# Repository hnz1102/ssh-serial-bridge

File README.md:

<div align="center">
  <h1><code>SSH Serial Bridge</code></h1>
  
</div>

# ssh-serial-bridge - SSH-to-Serial Bridge for Raspberry Pi, USB CDC and UART

Firmware for the ESP32-S3 that bridges an SSH connection (over Wi-Fi) to UART
and USB CDC serial ports.  Written in Rust (esp-idf-hal / esp-idf-svc) with a
C component (wolfSSH) for the SSH server.

## Features

| Feature | Description |
|---------|-------------|
| SSH server | Port 22, username/password authentication via wolfSSH, multiple concurrent sessions (including shared sessions on the same serial port) |
| Serial ports | COM1 / COM2 (UART) and USB CDC (USB Host) — up to 4 ports (`usb0`–`usb3`) |
| Web UI | Browser-based configuration, terminal, and GPIO control |
| WebSocket terminal | Built-in xterm.js; access serial data from the browser at `/terminal` |
| WPS support | Wi-Fi Protected Setup (PBC mode) — configure Wi-Fi via button or Web UI |
| GPIO / PWM | Digital output (ON/OFF) on GPIO 4–9, 12 ; PWM output on GPIO 10–11 |
| SPI display | Optional ST7789V (320×240) display showing incoming serial data |
| UDP Syslog | RFC 5424 remote logging over UDP |
| NTP | Time synchronisation on boot; up to 4 servers configurable via Web UI |
| NVS settings | Persistent configuration stored in NVS; editable via Web UI at runtime |

---

## Architecture

```
SSH client ──[TCP:22]──► ssh_bridge.c (wolfSSH)
                               │
        per-session ring buffers (PSRAM)
                               │
Rust usb_host.rs ◄─────────────┘
 ├── COM1 (UART1)
 ├── COM2 (UART2)
 └── USB CDC (USB Host: PL2303 / FTDI / etc.)

Browser ──[HTTP/WS]──► httpserver.rs
 ├── /terminal  (xterm.js + WebSocket /ws/serial)
 ├── /          (configuration page)
 └── /gpio      (GPIO/PWM control page)
```

---

## Directory Layout

```
ssh-serial-bridge/
├── src/
│   ├── main.rs           # Entry point, peripheral initialisation
│   ├── usb_host.rs       # USB Host (PL2303 etc.) + UART + SSH bridge control
│   ├── httpserver.rs     # HTTP/WebSocket server, NVS config management
│   ├── wifi.rs           # Wi-Fi STA connection (DHCP / static IP)
│   ├── syslogger.rs      # UDP Syslog logger (RFC 5424)
│   ├── serial_display.rs # ST7789V SPI display rendering
│   ├── gpio_ctrl.rs      # Shared GPIO / PWM state
│   ├── btn_ctrl.rs       # GPIO0 button (short press: page cycle; long press: factory reset)
│   └── boot_log.rs       # NVS boot counter and rolling reset-reason log (last 10 entries)
├── components/
│   ├── ssh_bridge/       # SSH server C component (wolfSSH wrapper)
│   ├── wolfssh/          # wolfSSH (github.com/wolfSSL/wolfssh, commit 157cb01f)
│   └── wolfssl/          # wolfSSL/wolfCrypt (github.com/wolfSSL/wolfssl, commit b7e7e755)
├── static/               # Embedded static files (xterm.js / css / fit addon)
├── cfg.toml              # Build-time default configuration (gitignored — contains credentials)
├── cfg.toml.<board>      # Board-specific templates (e.g. ssh-bridge-board / xiao-esp32s3)
├── sdkconfig.defaults    # ESP-IDF build settings
├── partitions.csv        # Flash partition table
├── build-flash-images.sh # Build merged flash + app-only OTA images per board
├── setup_components.sh   # Initial setup script for components/
└── setup_env.sh          # One-shot environment setup (Rust, espup, udev)
```

---

## Pin Assignment

### UART Serial

| Port | Signal | Default GPIO | XIAO-ESP32S3 |
|------|--------|-------------|--------------|
| COM1 | TX     | 17          | 43           |
| COM1 | RX     | 18          | 44           |
| COM2 | TX     | 19 (41)     | —            |
| COM2 | RX     | 20 (42)     | —            |

### GPIO / PWM Output

| GPIO    | Function |
|---------|----------|
| 4–9, 12 | Digital output ON/OFF |
| 10–11   | PWM output (LEDC, 1 kHz, 14-bit) |

### SPI Display (ST7789V)

| Signal | GPIO |
|--------|------|
| SCLK   | 48   |
| MOSI   | 45   |
| CS     | 40   |
| DC     | 39   |
| RST    | 38   |

### Button

| GPIO     | Function |
|----------|----------|
| 0 (BOOT) | Short press (<3 s): Cycle display page / Medium press (3–10 s): Toggle DC OUT (GPIO12) / Long press (≥10 s): NVS factory reset |
**Factory Reset Display Indicators:**
- **6–10 seconds** (button held): Display shows "FACTORY RESET" with countdown "Resetting to defaults in X seconds..."
- **10 seconds** (trigger): Display shows "FACTORY RESET" / "Erasing NVS... Please wait..." and device reboots
---

## Configuration

### Board-specific cfg.toml (build-time defaults)

Before building, choose a board config and copy it to `cfg.toml`.

- `ssh-bridge-board`: Board with a 2.0-inch TFT display for serial data output
- `mini-ssh-bridge-board`: Small-display board using SSD1306
- `xiao-esp32s3`: XIAO ESP32S3 board

```bash
# 2.0-inch TFT display board
cp cfg.toml.ssh-bridge-board cfg.toml

# SSD1306 mini display board
cp cfg.toml.mini-ssh-bridge-board cfg.toml

# XIAO ESP32S3 board
cp cfg.toml.xiao-esp32s3 cfg.toml
```

After copying, edit `cfg.toml` for your environment (Wi-Fi credentials, IP, etc.) if needed.

```toml
[ssh-serial-bridge]
wifi_ssid      = "your-ssid"
wifi_psk       = "your-password"
ip_mode        = "dhcp"           # "dhcp" or "static"
ip_address     = "192.168.2.200"
subnet_mask    = "255.255.255.0"
gateway        = "192.168.2.1"
dns            = "1.1.1.1"

syslog_server    = "192.168.2.140:514"
syslog_enable    = "false"
syslog_host_name = "esp32s3"
syslog_app_name  = "ssh-bridge"

ssh_user     = "admin"
ssh_password = "sshpass"

com1_tx_pin = "17"    # XIAO-ESP32S3: 43
com1_rx_pin = "18"    # XIAO-ESP32S3: 44
com1_baud   = "115200"
com2_tx_pin = "41"
com2_rx_pin = "42"
com2_baud   = "115200"

cdc_enable = "false"
cdc_baud   = "115200"

# CDC retry settings (for slow-initializing devices like Raspberry Pi USB Gadget)
cdc_retry_enable   = "true"    # Automatically retry CDC-ACM init until device is ready
cdc_retry_interval = "5"       # Seconds between retries (recommended: 5)

display_enable = "false"
display_port   = "com1"    # "com1" / "com2" / "usb0" / "usb1" / "usb2" / "usb3"

pwm_enable = "true"

# NTP servers (up to 4, in priority order)
ntp_server1 = "time.aws.com"
ntp_server2 = "time.google.com"
ntp_server3 = "time.cloudflare.com"
ntp_server4 = "ntp.nict.jp"

adc_conversion_factor = "74.47"　＃Factor to convert ADC reading to voltage (depends on voltage divider and reference voltage)
```

Values in `cfg.toml` are compiled into the firmware as defaults.  
After boot they can be overridden via the Web UI or direct NVS writes; NVS values take priority.

---

## Wi-Fi Setup with WPS

**WPS (Wi-Fi Protected Setup)** allows you to connect to a Wi-Fi network without manually entering the SSID and password. This device supports **WPS Push Button Configuration (PBC)** mode.

### Method 1: Using cfg.toml and Factory Reset (Recommended for initial setup)

If you don't have Wi-Fi credentials yet or want to reconfigure via WPS without Web UI access:

1. **Edit `cfg.toml` before building** (or rebuild the firmware):
   ```toml
   wifi_ssid      = ""           # Set to empty string
   wps_enable     = "true"       # Enable WPS mode on boot
   ```

2. **Flash the firmware** to the device

3. On boot, the device will automatically enter WPS mode and wait for you to **press the WPS button on your Wi-Fi router** (timeout: 2 minutes)

4. Upon successful WPS connection, the credentials are saved to NVS and the device reboots

**Alternative: Trigger WPS via Factory Reset**

If the device is already running with Wi-Fi configured but you want to switch to WPS:

1. **Edit `cfg.toml`** to set `wps_enable = "true"` and `wifi_ssid = ""`
2. **Rebuild and flash** the firmware
3. **Perform a Factory Reset**: Press and hold the BOOT button (GPIO 0) for **≥10 seconds**
4. The device will erase NVS, restore `cfg.toml` defaults, and reboot into WPS mode
5. **Press the WPS button on your Wi-Fi router** within 2 minutes

> **Note**: Web UI is not accessible until Wi-Fi is connected, so this method is essential for initial setup or when you lose Wi-Fi access.

---

### Method 2: Using the Web UI (when already connected to Wi-Fi)

1. Navigate to the configuration page at `http://<device_ip>/`
2. Find the **WPS** section
3. Click the **"Start WPS"** button
4. **Press the WPS button on your Wi-Fi router** within 2 minutes
5. The device will automatically receive and save the Wi-Fi credentials and reboot

### WPS Status Indicators

When WPS is active:
- **Display (if enabled)**: Shows "WPS MODE" with countdown timer (120 seconds)
  - "Press WPS button on your router within 120 seconds"
  - Countdown updates every 10 seconds
  - On success: "WPS SUCCESS" → "Connecting to {SSID}" → "CONNECTED"
- **Syslog (if enabled)**: Logs WPS start, success, or failure events
- **Web UI**: Shows WPS status during the connection process

### WPS Fallback

If WPS fails or times out, the device will revert to the previously configured Wi-Fi credentials (from `cfg.toml` or NVS).

### Notes

- WPS PBC mode is the only supported WPS method (PIN mode is not supported)
- After successful WPS configuration, the new credentials are saved to NVS and persist across reboots
- You can still manually configure Wi-Fi credentials via `cfg.toml` or the Web UI if WPS is not available on your router

---

## Environment Setup

Run `setup_env.sh` **once** on a fresh Ubuntu / Debian machine (or WSL2) before
building.  The script performs all steps below automatically.

```bash
bash setup_env.sh
```

After the script finishes, open a new terminal (or reload your shell config) so
the environment variables take effect:

```bash
source "$HOME/.cargo/env"
source ~/export-esp.sh
```

### What the script does

| Step | Action |
|------|--------|
| 1 | Install system packages via `apt` |
| 2 | Install Rust toolchain via `rustup` (skipped if already present) |
| 3 | Install `ldproxy`, `espup`, `cargo-espflash` via Cargo |
| 4 | Install & update the ESP32-S3 Xtensa toolchain via `espup` |
| 5 | Source `~/export-esp.sh` (generated by `espup`) |
| 6 | Add udev rule for ESP32 USB device (`303a:1001`) and reload rules |

> If you prefer to run the steps manually, expand each step below.

<details>
<summary>Manual setup steps</summary>

```bash
# 1. System packages
sudo apt update && sudo apt -y install \
    git python3 python3-pip gcc build-essential curl \
    pkg-config libudev-dev libtinfo5 clang libclang-dev \
    llvm-dev udev libssl-dev python3.10-venv

# 2. Rust
curl --proto '=https' --tlsv1.2 -sSf https://sh.rustup.rs | sh
# Select option 1 (default install), then:
source "$HOME/.cargo/env"

# 3. Cargo tools
cargo install ldproxy
cargo install espup
cargo install cargo-espflash

# 4. ESP32-S3 toolchain
espup install
espup update

# 5. Activate ESP environment (add to ~/.bashrc / ~/.zshrc for persistence)
. ~/export-esp.sh

# 6. udev rules
sudo sh -c 'echo "SUBSYSTEMS==\"usb\", ATTRS{idVendor}==\"303a\", ATTRS{idProduct}==\"1001\", MODE=\"0666\"" > /etc/udev/rules.d/99-esp32.rules'
sudo udevadm control --reload-rules
sudo udevadm trigger
```

</details>

---

## Build and Flash

### Prerequisites

- Rust toolchain: `esp` channel (selected automatically via `rust-toolchain.toml`)
- [espup](https://github.com/esp-rs/espup) — ESP32-S3 Xtensa toolchain
- [espflash](https://github.com/esp-rs/espflash)

### Initial component setup

Run once after cloning, or after a clean wipe of `components/`:

```bash
cd esp32-s3/ssh-serial-bridge
bash setup_components.sh
```

This clones wolfssh and wolfssl at the verified commits and places the
ESP-IDF-specific `CMakeLists.txt` and `include/user_settings.h` on top.

### Build

```bash
cargo build --release
```

### Flash and monitor

```bash
espflash flash --release --monitor
```

### Creating a complete flash binary image

To create a single binary file that includes all partitions (bootloader,
partition table, data partitions, and the currently built app image) for
distribution or web-based flashing:

```bash
cargo espflash save-image --release --merge --chip esp32s3 complete_flash.bin
```

This creates a complete 8 MB flash image starting from offset 0x0.

### Creating board images for both USB flashing and OTA

The helper script builds all board configs and produces both image types:

- `flash_images/flash_<board>.bin` (merged full-flash image, write at `0x0`)
- `flash_images/app_<board>.bin` (app-only image for `ssh ... update` OTA)

```bash
bash build-flash-images.sh
```

**Important**: When flashing this image, always write it to **offset 0x0**, not 0x9000. Writing to 0x9000 will result in a boot failure with "invalid header: 0xffffffff" error.

#### Flash the complete binary

```bash
# Using esptool.py
esptool.py --chip esp32s3 --port /dev/ttyUSB0 write_flash 0x0 complete_flash.bin

# Using espflash
espflash write-bin 0x0 complete_flash.bin
```

#### Web-based flashing (no command line required)

You can also flash the binary via a web browser using the ESP Web Flasher:

1. Open [https://thelastoutpostworkshop.github.io/ESPConnect/](https://thelastoutpostworkshop.github.io/ESPConnect/) in Chrome, Edge, or Opera (Web Serial API required)
2. Click **"Connect"** and select your ESP32-S3 device from the serial port list
3. Click **"Choose File"** and select `complete_flash.bin`
4. Set the flash address to **`0x0`** (very important!)
5. Click **"Program"** to start flashing
6. Wait for the process to complete and click **"Reset Device"**

This method is ideal for:
- Users without command-line tools installed
- Quick firmware updates without installing the Rust/ESP toolchain
- Distribution of pre-built binaries

### Flash layout

| Partition     | Offset  | Size   |
|---------------|---------|--------|
| nvs           | 0x9000  | 24 KB  |
| otadata       | 0xF000  | 8 KB   |
| phy_init      | 0x11000 | 4 KB   |
| ota_0 (app)   | 0x20000 | 4032 KB |
| ota_1 (app)   | 0x410000 | 4032 KB |

Flash: 8 MB, DIO mode, 40 MHz.

---

## Web UI Endpoints

### Web UI Snapshots

<div align="center">

</div>

| URL | Method | Description |
|-----|--------|-------------|
| `/login` | GET / POST | Login |
| `/logout` | GET | Logout |
| `/` | GET | Configuration page (auth required) |
| `/gpio` | GET | GPIO / PWM control page (auth required) |
| `/terminal` | GET | WebSocket serial terminal (auth required) |
| `/ws/serial` | WS | Bidirectional serial bridge |
| `/api/config` | POST | Save configuration to NVS |
| `/api/status` | GET | Device / Wi-Fi / USB status (JSON) |
| `/api/reset` | POST | Erase NVS and restore cfg.toml defaults |
| `/api/reboot` | POST | Reboot the device |
| `/api/gpio` | POST | Set one digital output ON/OFF |
| `/api/pwm` | POST | Set PWM duty cycle (0–100 %) |
| `/api/gpio_state` | GET | Current GPIO / PWM state (JSON) |
| `/api/boot_log` | GET | Boot history with reset reasons from NVS (JSON) |

---

## SSH Connection

### Authentication

| Item | Detail |
|------|--------|
| Port | 22 (TCP) |
| Auth method | Password only (public-key authentication is not supported) |
| Username | Any string is accepted — only the password is checked |
| Password | Set via `ssh_password` in `cfg.toml` or Web UI (default: `esp32`) |
| Concurrent sessions | Up to 6 total SSH sessions (including command sessions) |
| Per-device console sharing | Up to 4 concurrent console sessions on the same target (`usb0`-`usb3`, `com1`, `com2`) |

> **Security note:** Change the default password before deploying the device
> on a shared network.

---

### Commands

The SSH server dispatches on the command passed after the host.  
If no command is given, a usage summary is printed and the connection closes.

#### 1. Serial console bridge

Connects the SSH session as a transparent terminal to a serial port.

```bash
ssh -tt <user>@<device_ip> console (usb0|usb1|usb2|usb3|com1|com2)
```

| Argument | Description |
|----------|-------------|
| `usb0`   | First USB CDC device (plug order; alias: `usb`) |
| `usb1`   | Second USB CDC device |
| `usb2`   | Third USB CDC device |
| `usb3`   | Fourth USB CDC device |
| `com1`   | UART1 (pins configured by `com1_tx_pin` / `com1_rx_pin`) |
| `com2`   | UART2 (pins configured by `com2_tx_pin` / `com2_rx_pin`) |

- The `-tt` flag forces pseudo-TTY allocation, which is required for correct
  terminal behaviour.
- A welcome banner is printed on connect:
  ```
  Connected to ESP32-S3 SSH-Serial-Bridge v0.1.1 [com1].
  Disconnect: Enter then ~.
  ```
- The same serial target can be shared by multiple SSH clients.  When another
  session is already connected to that target, the banner also shows:
  ```
  Note: N other session(s) are also connected to this device — input/output is shared.
  ```
- Shared-session behaviour on the same target:
  - RX from device is broadcast to all connected SSH sessions on that target.
  - TX from each SSH session is sent to the same physical serial line, so input
    from multiple users can interleave.
- Capacity limits:
  - Max 4 console sessions per target (`com1`, `com2`, `usb0`-`usb3`).
  - Max 6 total SSH sessions across the system.
- If a target already has 4 console sessions, new attempts are rejected with:
  ```
  Error: too many sessions already connected to this device (max 4).
  ```
- Serial data received before the first keystroke from the SSH client is
  discarded to prevent stale output flooding the terminal on login.
- Disconnect with the standard OpenSSH escape sequence: press **Enter**, then
  type **`~.`**

**Examples:**

```bash
# Connect to the first USB CDC device
ssh -tt admin@192.168.2.200 console usb0

# Connect to the second USB CDC device
ssh -tt admin@192.168.2.200 console usb1

# Connect to COM1 (UART1)
ssh -tt admin@192.168.2.200 console com1

# Connect to COM2 (UART2)
ssh -tt admin@192.168.2.200 console com2
```

---

#### 2. GPIO digital output control

Controls GPIO4–GPIO9 output pins (mapped as power outlets 1–6).

```bash
ssh <user>@<device_ip> power <1-6> (on|off)
```

| Argument | Description |
|----------|-------------|
| `1`–`6`  | Outlet number: 1 = GPIO4, 2 = GPIO5, … 6 = GPIO9 |
| `on`     | Set output HIGH |
| `off`    | Set output LOW  |

**Examples:**

```bash
ssh admin@192.168.2.200 power 1 on    # GPIO4 → HIGH
ssh admin@192.168.2.200 power 3 off   # GPIO6 → LOW
```

---

#### 3. DC Power output control (GPIO12)

Controls the dedicated DC Power output on GPIO12.

```bash
ssh <user>@<device_ip> dcpower (on|off)
```

**Examples:**

```bash
ssh admin@192.168.2.200 dcpower on
ssh admin@192.168.2.200 dcpower off
```

---

#### 4. DC Power power-cycle (GPIO12)

Turns the DC Power output off, waits briefly, then turns it back on — in a single SSH call.

```bash
ssh <user>@<device_ip> powercycle
```

**Example:**

```bash
ssh admin@192.168.2.200 powercycle
```

---

#### 5. PWM duty cycle control

Sets the PWM duty cycle on GPIO10 or GPIO11 (LEDC, 1 kHz, 14-bit).

```bash
ssh <user>@<device_ip> pwm <1|2> <0-100>
```

| Argument | Description |
|----------|-------------|
| `1`      | Channel 1 — GPIO10 |
| `2`      | Channel 2 — GPIO11 |
| `0`–`100`| Duty cycle in percent |

**Examples:**

```bash
ssh admin@192.168.2.200 pwm 1 50    # GPIO10 → 50 %
ssh admin@192.168.2.200 pwm 2 0     # GPIO11 → off
ssh admin@192.168.2.200 pwm 1 100   # GPIO10 → full on
```

---

#### 6. Reboot the device

Reboots the ESP32-S3 (equivalent to a power-on reset).

```bash
ssh <user>@<device_ip> reboot
```

**Example:**

```bash
ssh admin@192.168.2.200 reboot
```

---

#### 7. OTA firmware update

Streams a new app image over SSH directly into the inactive OTA partition, then
reboots into it. No filesystem, SCP, or SFTP support is required — the exec
channel's stdin is piped straight into flash.

```bash
ssh <user>@<device_ip> update < firmware.bin
```

**Example:**

```bash
cat flash_images/app_ssh-bridge-board.bin | ssh admin@192.168.2.200 update
```

**Important:**

- Use the **app-only** image (`flash_images/app_<board>.bin`, produced by
  `build-flash-images.sh`), **not** the merged full-flash image
  (`flash_images/flash_<board>.bin`). The merged image includes the
  bootloader and partition table baked in at offset 0 and will corrupt the
  OTA partition if written this way.
- The device has two OTA app slots (`ota_0`/`ota_1`). The update is written to
  whichever slot isn't currently running, so the previous firmware is left
  untouched until the new image is fully received and verified.
- **Rollback safety:** the new image boots in a "pending verify" state. Once
  the SSH bridge starts successfully it is marked valid automatically. If the
  new firmware crashes or fails to boot before that point, the bootloader
  automatically reverts to the previous working firmware on the next reset.
- This requires the partition table to include `ota_0`/`ota_1`/`otadata`
  (see `partitions.csv`). Boards flashed with an older single-partition image
  must be reflashed once via USB/serial (`cargo espflash flash` or the merged
  `flash_<board>.bin` image) before OTA updates over SSH will work.

---

### Usage summary (printed on unknown command)

```
ESP32-S3 SSH-Serial-Bridge
Usage:
  ssh -tt admin@host console (usb0|usb1|usb2|usb3|com1|com2)  -- Serial console bridge
  ssh    admin@host power   (1-6) (on|off)    -- GPIO4-9 output control
  ssh    admin@host dcpower (on|off)          -- DC Power output (GPIO12)
  ssh    admin@host powercycle                -- DC Power off->on (GPIO12)
  ssh    admin@host pwm   (1|2) (0-100)       -- PWM GPIO10-11 duty %
  ssh    admin@host reboot                    -- Reboot the ESP32-S3
  ssh    admin@host update < firmware.bin      -- OTA firmware update
```

---

## Supported USB CDC Devices

The USB Host driver auto-detects the connected adapter by VID/PID and applies
the appropriate initialisation sequence.  The baud rate is set by `cdc_baud`
in `cfg.toml` (default: `115200`).

> **Note:** `cdc_enable` must be set to `"true"` in `cfg.toml` (or via Web UI)
> to activate the USB Host driver.  When disabled, `usb0`–`usb3` are
> unavailable as SSH console targets.

### Vendor-class adapters

| Chip | VID | PID(s) | Ports | Notes |
|------|-----|--------|-------|-------|
| **PL2303** | `067B` | `2303`, `23A3`, `2304` | 1 | Prolific Technology |
| **CP210x** | `10C4` | `EA60`, `EA61`, `EA70` | 1 | Silicon Labs |
| **FT232R** | `0403` | `6001` | 1 | FTDI |
| **FT232H** | `0403` | `6014` | 1 | FTDI |
| **FT2232H/D** | `0403` | `6010` | 2 | FTDI — maps to `usb0` / `usb1` |
| **FT4232H** | `0403` | `6011` | 4 | FTDI — maps to `usb0`–`usb3` |

### Linux USB Gadget (Raspberry Pi)

This firmware supports **Raspberry Pi USB Gadget mode** for direct serial access over USB:

| Device | VID | PID | Module | Notes |
|--------|-----|-----|--------|-------|
| **Raspberry Pi (g_cdc)** | `0525` | `a4a7` | `g_cdc` | CDC-ACM composite device (recommended) |

#### Raspberry Pi Configuration

To use your Raspberry Pi as a USB serial gadget with this ESP32-S3 bridge:

1. **Enable USB gadget mode** on your Raspberry Pi:
   ```bash
   # Add to /boot/config.txt (or /boot/firmware/config.txt on Ubuntu)
   dtoverlay=dwc2
   ```

2. **Load the g_cdc module** (recommended over g_serial):
   
   **Method A: Using cmdline.txt (Recommended)**
   ```bash
   # Edit /boot/cmdline.txt (or /boot/firmware/cmdline.txt on Ubuntu)
   # Add modules-load=dwc2,g_cdc to the kernel command line
   # Example:
   console=serial0,115200 ... modules-load=dwc2,g_cdc ...
   ```
   
   **Method B: Using /etc/modules**
   ```bash
   # Add to /etc/modules
   dwc2
   g_cdc
   ```

3. **Enable serial-getty service** (required for the CDC device to respond):
   ```bash
   sudo systemctl enable serial-getty@ttyGS0
   sudo systemctl start serial-getty@ttyGS0
   ```

4. **Reboot your Raspberry Pi**:
   ```bash
   sudo reboot
   ```

5. **Connect the Pi to the ESP32-S3 USB port** using a USB cable

> **Important:** Use `g_cdc` instead of `g_serial`. The `g_serial` module has compatibility issues with the ESP-IDF USB Host stack and may not work reliably. `g_cdc` provides better standards compliance and works seamlessly with this firmware.

After configuration, the Pi will appear as a CDC-ACM device and you can access its serial console via SSH to the ESP32-S3 bridge (target: `usb0`).

### Port mapping

Multi-port FTDI adapters expose multiple ports, mapped to SSH console targets
in channel order:

| SSH target | Description |
|------------|-------------|
| `usb0` | Port 1 — all single-port adapters; FT2232 ch.A; FT4232 ch.A |
| `usb1` | Port 2 — FT2232 ch.B; FT4232 ch.B |
| `usb2` | Port 3 — FT4232 ch.C |
| `usb3` | Port 4 — FT4232 ch.D |

---

## Dependencies

| Component / Library | Version | License | Purpose |
|---------------------|---------|---------|---------|
| **ssh-serial-bridge** (this project) | 0.1.1 | MIT | Firmware (Rust) |
| **ssh_bridge** component | 0.1.1 | MIT | SSH server C wrapper |
| esp-idf-hal | 0.45.2 | MIT / Apache-2.0 | ESP32-S3 hardware abstraction |
| esp-idf-svc | 0.51 | MIT / Apache-2.0 | Wi-Fi, HTTP server, SNTP, etc. |
| **wolfSSH** | commit `157cb01f` | GPLv3 (or commercial) | SSH server protocol |
| **wolfSSL / wolfCrypt** | commit `b7e7e755` | GPLv3 (or commercial) | Cryptography library |
| mipidsi | 0.8.0 | MIT | ST7789V display driver |
| embedded-graphics | 0.8.1 | MIT | Display rendering |
| @xterm/xterm | 6.0.0 (bundled) | MIT | Browser WebSocket terminal |
| @xterm/addon-fit | 0.11.0 (bundled) | MIT | xterm.js terminal fit addon |

> **Note on wolfSSH / wolfSSL licensing:**  
> Both wolfSSH and wolfSSL are dual-licensed under **GPLv3** (open source) or a
> **commercial license** (for use in proprietary products).

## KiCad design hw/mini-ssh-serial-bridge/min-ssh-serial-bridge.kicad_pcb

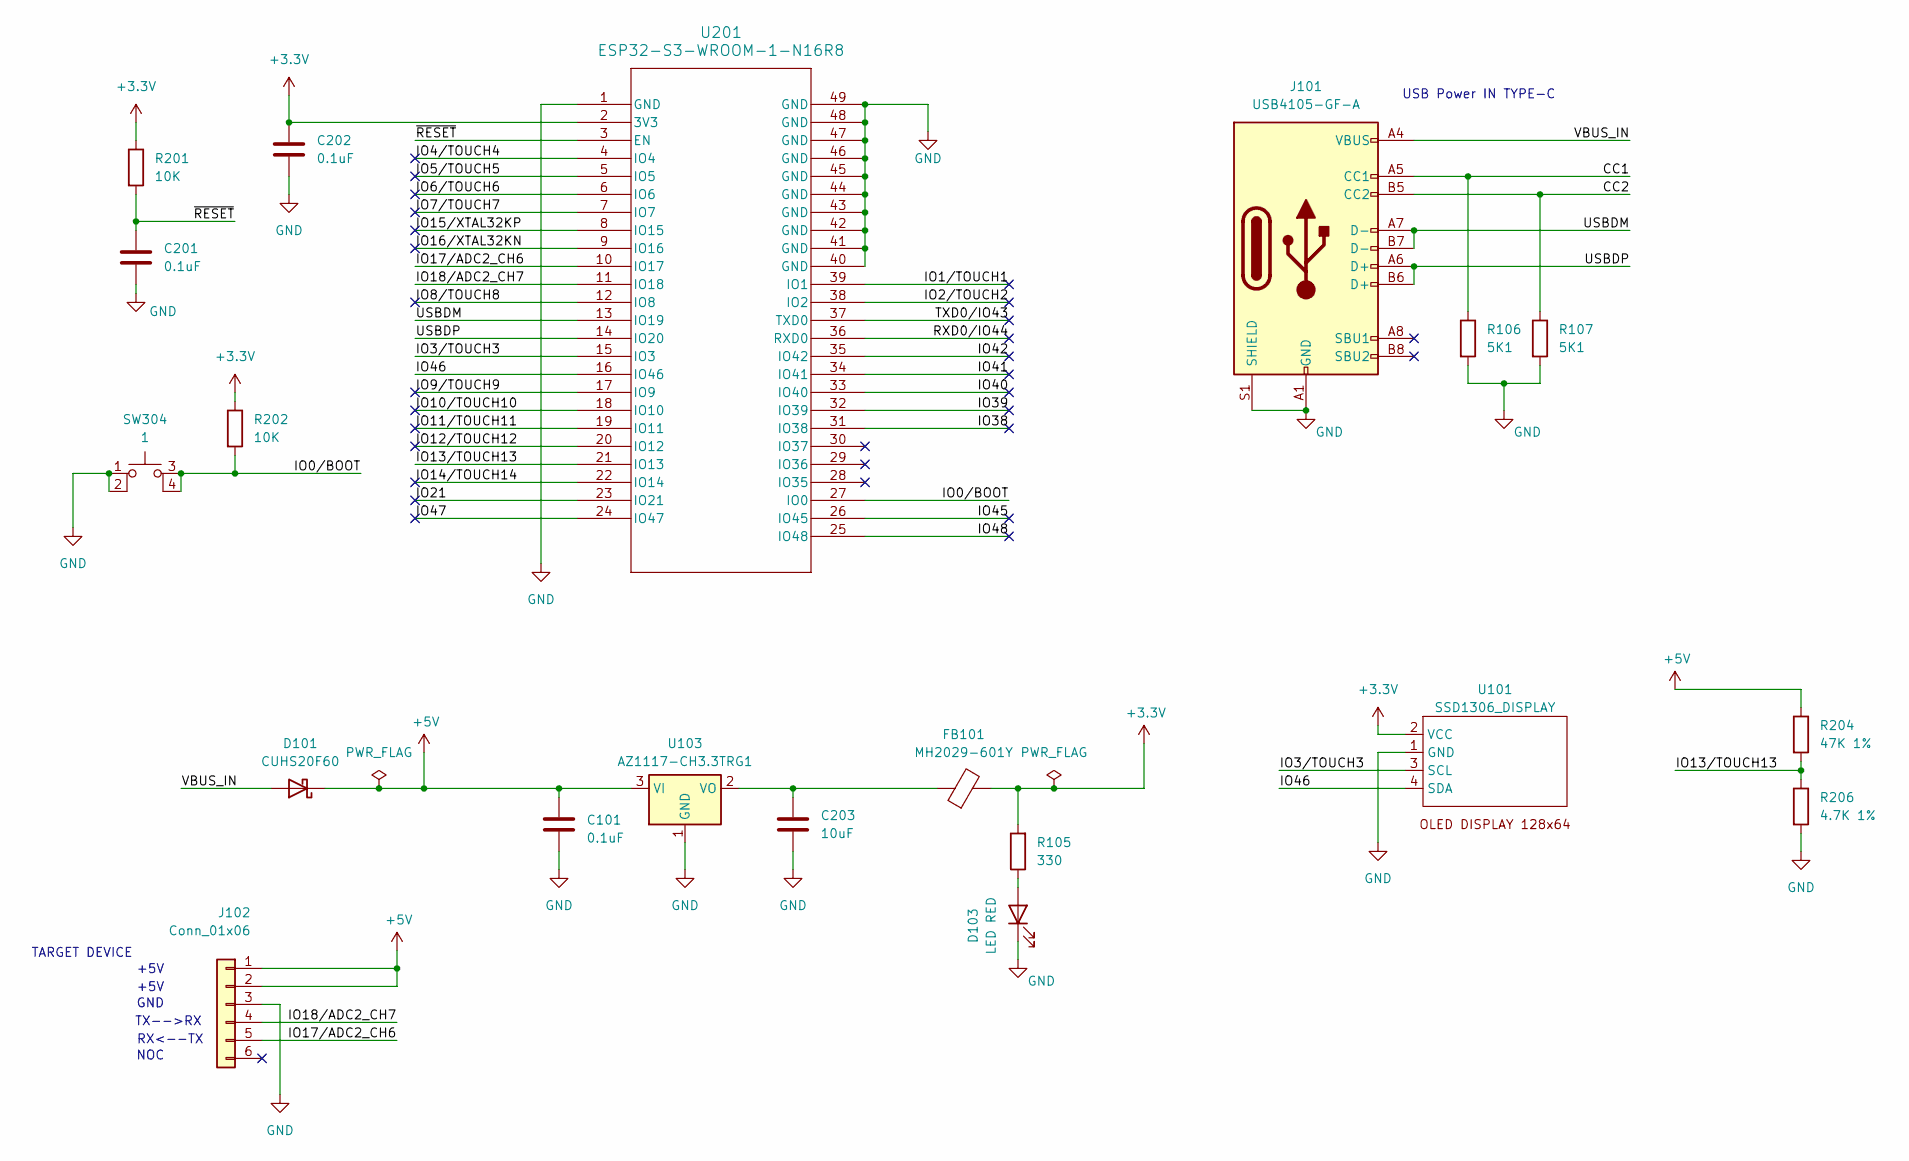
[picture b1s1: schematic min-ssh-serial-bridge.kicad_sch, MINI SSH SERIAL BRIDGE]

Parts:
C101, C201, C202: 0.1uF; C_0603_1608Metric; digikey 311-1343-1-ND
C203: 10uF; C_0805_2012Metric; digikey 311-1355-1-ND
D101: CUHS20F60; D_PowerDI-123; digikey 264-CUHS20F60H3FCT-ND
D103: LED RED; LED_0603_1608Metric; digikey 3147-B1931URO-20D000114U1930CT-ND
FB101: MH2029-601Y; L_0805_2012Metric; digikey MH2029-601YCT-ND
J101: USB4105-GF-A; USB_C_5077CR-16-SMC2-BK-TR; digikey 2073-USB4105-GF-ACT-ND
J102: Conn_01x06; PinHeader_1x06_P2.54mm_Vertical; digikey S5442-ND
R105: 330; R_0603_1608Metric; digikey 13-RC0603JR-13330RLCT-ND
R106, R107: 5K1; R_0603_1608Metric; digikey 311-5.10KHRCT-ND
R201, R202: 10K; R_0603_1608Metric; digikey 311-10.0KHRCT-ND
R204: 47K 1%; R_0603_1608Metric; digikey 311-47.0KHRCT-ND
R206: 4.7K 1%; R_0603_1608Metric; digikey 311-4.70KHRCT-ND
SW304: 1; SW_SKRPACE010_4mm_3mm; digikey P12298SCT-ND
U101: SSD1306_DISPLAY; OLED I2C DISPLAY
U103: AZ1117-CH3.3TRG1; SOT-223-3_TabPin2; digikey AZ1117CH-3.3TRG1DICT-ND
U201: ESP32-S3-WROOM-1-N16R8; ESP32-S3-WROOM-1_EXP; digikey 1965-ESP32-S3-WROOM-1-N16R8CT-ND

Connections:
+3.3V: C202.1, FB101.2, R105.2, R201.1, R202.1, U101.2 (VCC), U201.2 (3V3)
+5V: C101.1, D101.1 (K), J102.1, J102.2, R204.1, U103.3 (VI)
/CC1: J101.A5 (CC1), R106.1
/CC2: J101.B5 (CC2), R107.1
/IO0/BOOT: R202.2, SW304.3, SW304.4, U201.27 (IO0)
/IO1/TOUCH1: U201.39 (IO1)
/IO2/TOUCH2: U201.38 (IO2)
/IO3/TOUCH3: U101.3 (SCL), U201.15 (IO3)
/IO4/TOUCH4: U201.4 (IO4)
/IO5/TOUCH5: U201.5 (IO5)
/IO6/TOUCH6: U201.6 (IO6)
/IO7/TOUCH7: U201.7 (IO7)
/IO8/TOUCH8: U201.12 (IO8)
/IO9/TOUCH9: U201.17 (IO9)
/IO10/TOUCH10: U201.18 (IO10)
/IO11/TOUCH11: U201.19 (IO11)
/IO12/TOUCH12: U201.20 (IO12)
/IO13/TOUCH13: R204.2, R206.1, U201.21 (IO13)
/IO14/TOUCH14: U201.22 (IO14)
/IO15/XTAL32KP: U201.8 (IO15)
/IO16/XTAL32KN: U201.9 (IO16)
/IO17/ADC2_CH6: J102.5, U201.10 (IO17)
/IO18/ADC2_CH7: J102.4, U201.11 (IO18)
/IO21: U201.23 (IO21)
/IO38: U201.31 (IO38)
/IO39: U201.32 (IO39)
/IO40: U201.33 (IO40)
/IO41: U201.34 (IO41)
/IO42: U201.35 (IO42)
/IO45: U201.26 (IO45)
/IO46: U101.4 (SDA), U201.16 (IO46)
/IO47: U201.24 (IO47)
/IO48: U201.25 (IO48)
/RXD0/IO44: U201.36 (RXD0)
/TXD0/IO43: U201.37 (TXD0)
/USBDM: J101.A7 (D-), J101.B7 (D-), U201.13 (IO19)
/USBDP: J101.A6 (D+), J101.B6 (D+), U201.14 (IO20)
/VBUS_IN: D101.2 (A), J101.A4 (VBUS), J101.A9 (VBUS), J101.B4 (VBUS), J101.B9 (VBUS)
/~RESET: C201.1, R201.2, U201.3 (EN)
GND: C101.2, C201.2, C202.2, C203.2, D103.1 (K), J101.A1 (GND), J101.A12 (GND), J101.B1 (GND), J101.B12 (GND), J101.S1 (SHIELD), J102.3, R106.2, R107.2, R206.2, SW304.1, SW304.2, U101.1 (GND), U103.1 (GND), U201.1 (GND), U201.40 (GND), U201.41 (GND), U201.42 (GND), U201.43 (GND), U201.44 (GND), U201.45 (GND), U201.46 (GND), U201.47 (GND), U201.48 (GND), U201.49 (GND)
unnamed: D103.2 (A), R105.1
unnamed: C203.1, FB101.1, U103.2 (VO)

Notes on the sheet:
RX<--TX
USB Power IN TYPE-C
TARGET DEVICE
NOC
+5V
TX-->RX
GND

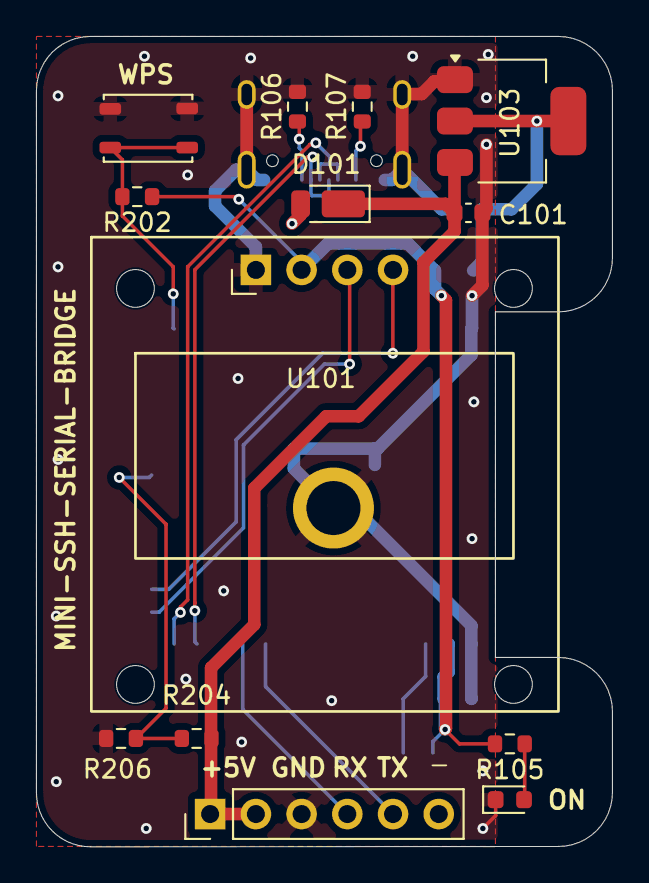
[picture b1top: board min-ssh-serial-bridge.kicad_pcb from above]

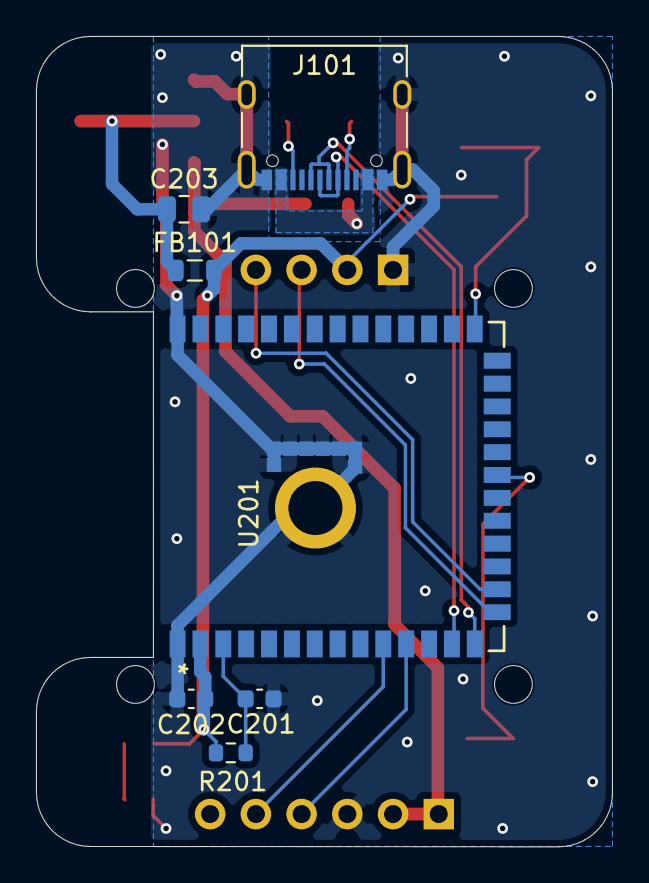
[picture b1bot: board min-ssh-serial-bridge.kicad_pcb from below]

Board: 2 copper layers, 32.0 x 45.0 mm, 20 parts (7 on the bottom side), 17 nets.

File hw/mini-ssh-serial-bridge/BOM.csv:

"Reference","Qty","Value","DNP","Exclude from BOM","Exclude from Board","Footprint","digikey"
"C101,C201,C202","3","0.1uF","","","","Capacitor_SMD:C_0603_1608Metric","311-1343-1-ND"
"C203","1","10uF","","","","Capacitor_SMD:C_0805_2012Metric","311-1355-1-ND"
"D101","1","CUHS20F60","","","","Diode_SMD:D_PowerDI-123","264-CUHS20F60H3FCT-ND"
"D103","1","LED RED","","","","LED_SMD:LED_0603_1608Metric","3147-B1931URO-20D000114U1930CT-ND"
"FB101","1","MH2029-601Y","","","","Inductor_SMD:L_0805_2012Metric","MH2029-601YCT-ND"
"J101","1","USB4105-GF-A","","","","tbctl:USB_C_5077CR-16-SMC2-BK-TR","2073-USB4105-GF-ACT-ND"
"J102","1","Conn_01x06","","","","Connector_PinHeader_2.54mm:PinHeader_1x06_P2.54mm_Vertical","S5442-ND"
"R105","1","330","","","","Resistor_SMD:R_0603_1608Metric","13-RC0603JR-13330RLCT-ND"
"R106,R107","2","5K1","","","","Resistor_SMD:R_0603_1608Metric","311-5.10KHRCT-ND"
"R201,R202","2","10K","","","","Resistor_SMD:R_0603_1608Metric","311-10.0KHRCT-ND"
"R204","1","47K 1%","","","","Resistor_SMD:R_0603_1608Metric","311-47.0KHRCT-ND"
"R206","1","4.7K 1%","","","","Resistor_SMD:R_0603_1608Metric","311-4.70KHRCT-ND"
"SW304","1","1","","","","tbctl:SW_SKRPACE010_4mm_3mm","P12298SCT-ND"
"U101","1","SSD1306_DISPLAY","","","","tbctl:OLED I2C DISPLAY","https://akizukidenshi.com/catalog/g/g112031/"
"U103","1","AZ1117-CH3.3TRG1","","","","Package_TO_SOT_SMD:SOT-223-3_TabPin2","AZ1117CH-3.3TRG1DICT-ND"
"U201","1","ESP32-S3-WROOM-1-N16R8","","","","tbctl:ESP32-S3-WROOM-1_EXP","1965-ESP32-S3-WROOM-1-N16R8CT-ND"

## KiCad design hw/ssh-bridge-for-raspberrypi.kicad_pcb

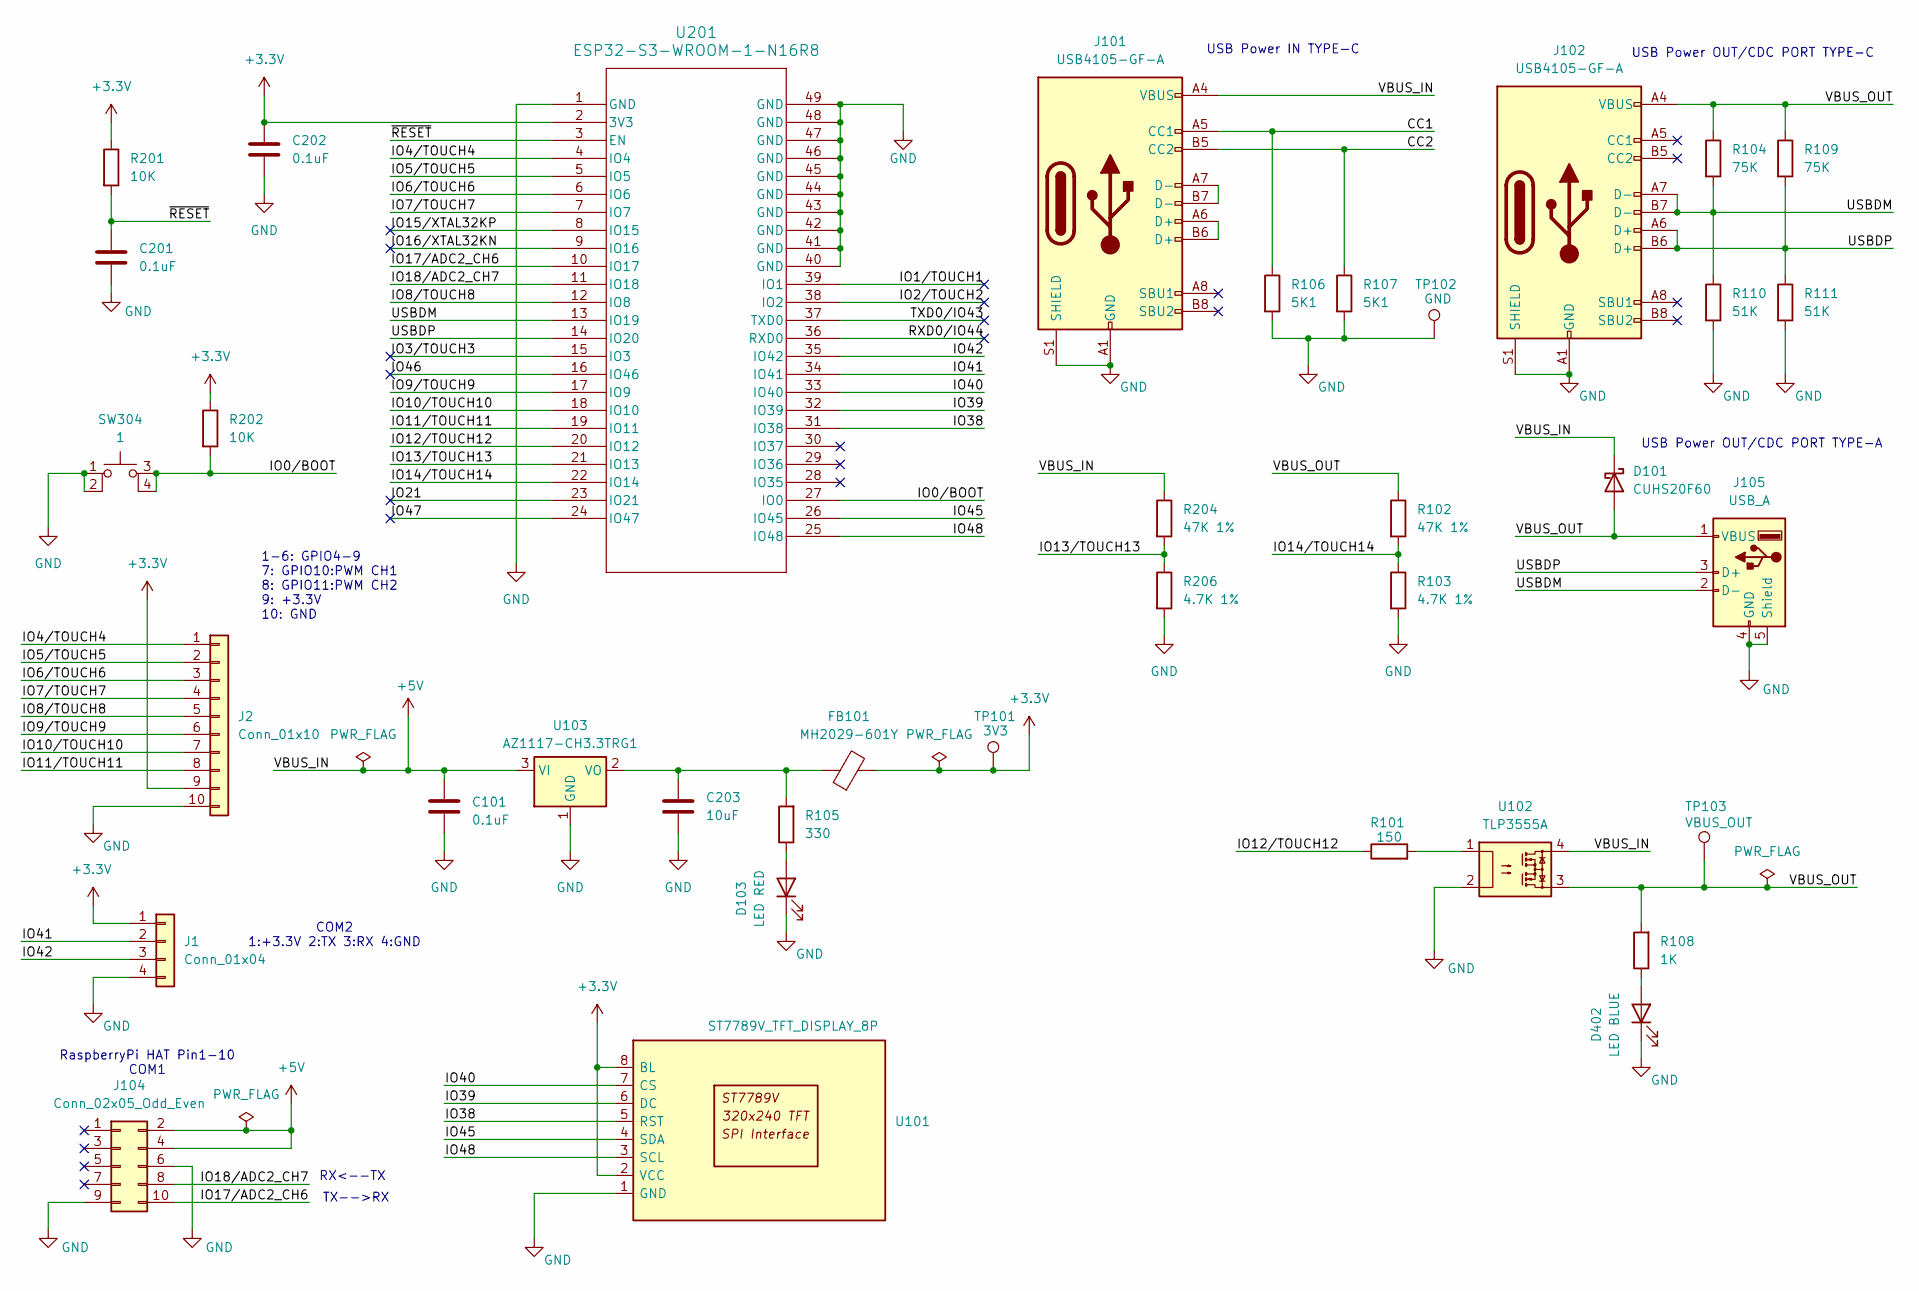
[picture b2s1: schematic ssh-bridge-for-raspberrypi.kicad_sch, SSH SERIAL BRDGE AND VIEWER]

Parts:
C101, C201, C202: 0.1uF; C_0603_1608Metric; digikey 311-1343-1-ND
C203: 10uF; C_0805_2012Metric; digikey 311-1355-1-ND
D101: CUHS20F60; D_PowerDI-123; digikey 264-CUHS20F60H3FCT-ND
D103: LED RED; LED_0603_1608Metric; digikey 3147-B1931URO-20D000114U1930CT-ND
D402: LED BLUE; LED_0603_1608Metric; digikey 3147-B1931NB--20C007614U1930CT-ND
FB101: MH2029-601Y; L_0805_2012Metric; digikey MH2029-601YCT-ND
J1: Conn_01x04; PinHeader_1x04_P2.54mm_Vertical; digikey 732-5317-ND
J2: Conn_01x10; PinHeader_1x10_P2.54mm_Vertical; digikey 732-2670-ND
J101, J102: USB4105-GF-A; USB_C_5077CR-16-SMC2-BK-TR; digikey 2073-USB4105-GF-ACT-ND
J104: Conn_02x05_Odd_Even; PinHeader_2x05_P2.54mm_Vertical; digikey 732-2672-ND
J105: USB_A; USB_A_5075AR-04; digikey ED2989-ND
R101: 150; R_0603_1608Metric; digikey 13-RC0603FR-13150RLCT-ND
R102, R204: 47K 1%; R_0603_1608Metric; digikey 311-47.0KHRCT-ND
R103, R206: 4.7K 1%; R_0603_1608Metric; digikey 311-4.70KHRCT-ND
R104, R109: 75K; R_0603_1608Metric; digikey 311-75.0KHRCT-ND
R105: 330; R_0603_1608Metric; digikey 13-RC0603JR-13330RLCT-ND
R106, R107: 5K1; R_0603_1608Metric; digikey 311-5.10KHRCT-ND
R108: 1K; R_0603_1608Metric; digikey 311-1.00KHRCT-ND
R110, R111: 51K; R_0603_1608Metric; digikey 311-51.0KHRCT-ND
R201, R202: 10K; R_0603_1608Metric; digikey 311-10.0KHRCT-ND
SW304: 1; SW_SKRPACE010_4mm_3mm; digikey P12298SCT-ND
TP101: 3V3; TestPoint_Pad_D1.0mm
TP102: GND; TestPoint_Pad_D1.0mm
TP103: VBUS_OUT; TestPoint_Pad_D1.0mm
U101: ST7789V_TFT_DISPLAY_8P; ST7789V TFT SPI DISPLAY 320x240 GMT020-02-8P
U102: TLP3555A; DIP-4_W7.62mm; digikey TLP3555A(F-ND
U103: AZ1117-CH3.3TRG1; SOT-223-3_TabPin2; digikey AZ1117CH-3.3TRG1DICT-ND
U201: ESP32-S3-WROOM-1-N16R8; ESP32-S3-WROOM-1_EXP; digikey 1965-ESP32-S3-WROOM-1-N16R8CT-ND

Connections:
+3.3V: C202.1, FB101.2, J1.1, J2.9, R201.1, R202.1, TP101.1 (1_1), U101.2 (VCC), U101.8 (BL), U201.2 (3V3)
+5V: C101.1, D101.1 (K), J101.A4 (VBUS), J101.A9 (VBUS), J101.B4 (VBUS), J101.B9 (VBUS), J104.2, J104.4, R204.1, U102.4, U103.3 (VI)
/CC1: J101.A5 (CC1), R106.1
/CC2: J101.B5 (CC2), R107.1
/IO0/BOOT: R202.2, SW304.3, SW304.4, U201.27 (IO0)
/IO1/TOUCH1: U201.39 (IO1)
/IO2/TOUCH2: U201.38 (IO2)
/IO3/TOUCH3: U201.15 (IO3)
/IO4/TOUCH4: J2.1, U201.4 (IO4)
/IO5/TOUCH5: J2.2, U201.5 (IO5)
/IO6/TOUCH6: J2.3, U201.6 (IO6)
/IO7/TOUCH7: J2.4, U201.7 (IO7)
/IO8/TOUCH8: J2.5, U201.12 (IO8)
/IO9/TOUCH9: J2.6, U201.17 (IO9)
/IO10/TOUCH10: J2.7, U201.18 (IO10)
/IO11/TOUCH11: J2.8, U201.19 (IO11)
/IO12/TOUCH12: R101.1, U201.20 (IO12)
/IO13/TOUCH13: R204.2, R206.1, U201.21 (IO13)
/IO14/TOUCH14: R102.2, R103.1, U201.22 (IO14)
/IO15/XTAL32KP: U201.8 (IO15)
/IO16/XTAL32KN: U201.9 (IO16)
/IO17/ADC2_CH6: J104.10, U201.10 (IO17)
/IO18/ADC2_CH7: J104.8, U201.11 (IO18)
/IO21: U201.23 (IO21)
/IO38: U101.5 (RST), U201.31 (IO38)
/IO39: U101.6 (DC), U201.32 (IO39)
/IO40: U101.7 (CS), U201.33 (IO40)
/IO41: J1.2, U201.34 (IO41)
/IO42: J1.3, U201.35 (IO42)
/IO45: U101.4 (SDA), U201.26 (IO45)
/IO46: U201.16 (IO46)
/IO47: U201.24 (IO47)
/IO48: U101.3 (SCL), U201.25 (IO48)
/RXD0/IO44: U201.36 (RXD0)
/TXD0/IO43: U201.37 (TXD0)
/USBDM: J102.A7 (D-), J102.B7 (D-), J105.2 (D-), R104.2, R110.1, U201.13 (IO19)
/USBDP: J102.A6 (D+), J102.B6 (D+), J105.3 (D+), R109.2, R111.1, U201.14 (IO20)
/VBUS_OUT: D101.2 (A), J102.A4 (VBUS), J102.A9 (VBUS), J102.B4 (VBUS), J102.B9 (VBUS), J105.1 (VBUS), R102.1, R104.1, R108.2, R109.1, TP103.1 (1_1), U102.3
/~RESET: C201.1, R201.2, U201.3 (EN)
GND: C101.2, C201.2, C202.2, C203.2, D103.1 (K), D402.1 (K), J1.4, J2.10, J101.A1 (GND), J101.A12 (GND), J101.B1 (GND), J101.B12 (GND), J101.S1 (SHIELD), J102.A1 (GND), J102.A12 (GND), J102.B1 (GND), J102.B12 (GND), J102.S1 (SHIELD), J104.6, J104.9, J105.4 (GND), J105.5 (Shield), R103.2, R106.2, R107.2, R110.2, R111.2, R206.2, SW304.1, SW304.2, TP102.1 (1_1), U101.1 (GND), U102.2, U103.1 (GND), U201.1 (GND), U201.40 (GND), U201.41 (GND), U201.42 (GND), U201.43 (GND), U201.44 (GND), U201.45 (GND), U201.46 (GND), U201.47 (GND), U201.48 (GND), U201.49 (GND)
unnamed: D103.2 (A), R105.1
unnamed: D402.2 (A), R108.1
unnamed: J101.A6 (D+), J101.B6 (D+)
unnamed: J101.A7 (D-), J101.B7 (D-)
unnamed: R101.2, U102.1
unnamed: C203.1, FB101.1, R105.2, U103.2 (VO)

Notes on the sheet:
USB Power OUT/CDC PORT TYPE-A
COM2 1:+3.3V 2:TX 3:RX 4:GND
1-6: GPIO4-9 7: GPIO10:PWM CH1 8: GPIO11:PWM CH2 9: +3.3V 10: GND
USB Power IN TYPE-C
RaspberryPi HAT Pin1-10 COM1
TX-->RX
USB Power OUT/CDC PORT TYPE-C
RX<--TX

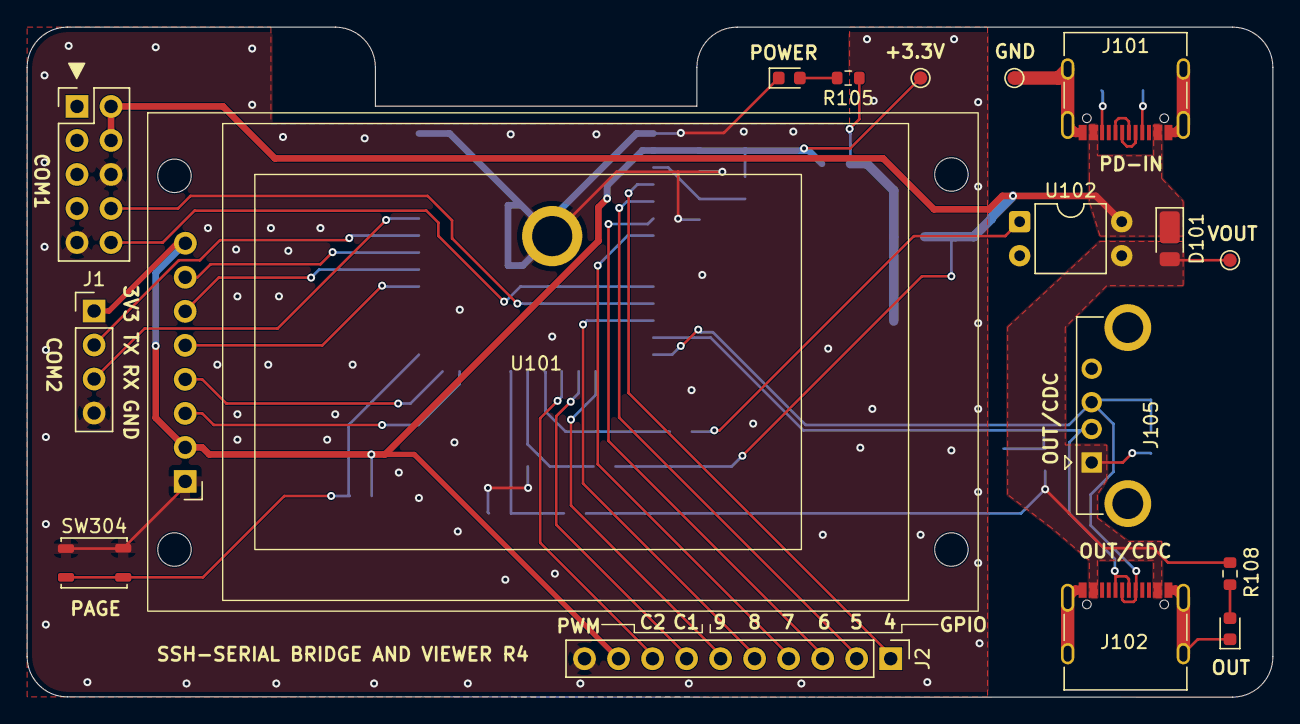
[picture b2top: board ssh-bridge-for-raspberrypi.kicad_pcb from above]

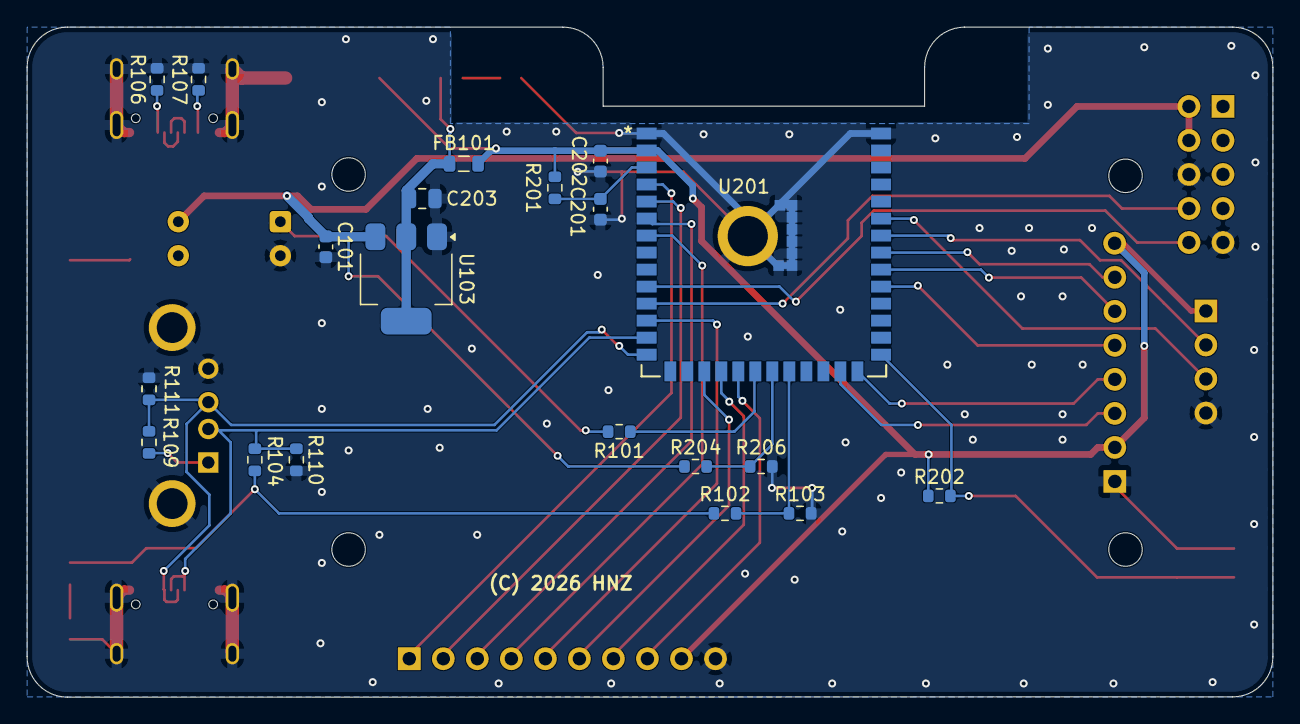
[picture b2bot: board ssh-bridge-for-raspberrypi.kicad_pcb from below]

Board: 2 copper layers, 93.0 x 50.0 mm, 37 parts (20 on the bottom side), 36 nets.

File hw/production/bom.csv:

Designator,Footprint,Quantity,Value,LCSC Part #
"C101, C201, C202",0603,3,0.1uF,
C203,0805,1,10uF,
D101,D_PowerDI-123,1,CUHS20F60,
D103,0603,1,LED RED,
D402,0603,1,LED BLUE,
FB101,0805,1,MH2029-601Y,
J1,PinHeader_1x04_P2.54mm_Vertical,1,Conn_01x04,
"J101, J102",USB_C_5077CR-16-SMC2-BK-TR,2,USB4105-GF-A,
J104,PinHeader_2x05_P2.54mm_Vertical,1,Conn_02x05_Odd_Even,
J105,USB_A_5075AR-04,1,USB_A,
J2,PinHeader_1x10_P2.54mm_Vertical,1,Conn_01x10,
R101,0603,1,150,
"R102, R204",0603,2,47K 1%,
"R103, R206",0603,2,4.7K 1%,
"R104, R109",0603,2,75K,
R105,0603,1,330,
"R106, R107",0603,2,5K1,
R108,0603,1,1K,
"R110, R111",0603,2,51K,
"R201, R202",0603,2,10K,
SW304,SW_SKRPACE010_4mm_3mm,1,1,
TP101,TestPoint_Pad_D1.0mm,1,3V3,
TP102,TestPoint_Pad_D1.0mm,1,GND,
TP103,TestPoint_Pad_D1.0mm,1,VBUS_OUT,
U101,ST7789V TFT SPI DISPLAY 320x240 GMT020-02-8P,1,ST7789V_TFT_DISPLAY_8P,
U102,DIP-4_W7.62mm,1,TLP3555A,
U103,SOT-223-3_TabPin2,1,AZ1117-CH3.3TRG1,
U201,ESP32-S3-WROOM-1_EXP,1,ESP32-S3-WROOM-1-N16R8,

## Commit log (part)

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2026-04-15 Change componet_dirs path
2026-04-15 Fixed compile error
2026-04-20 Fixed ssh-serial bridge received buffer
2026-04-21 Add turn on/off for dcout
2026-04-21 Fixed build error
2026-04-22 Fixed USB-CDC port select. Add NTP servers are configureble setting and PWM enable/disable setting
2026-04-23 Add setup environment
2026-04-23 Add power source detection
2026-04-23 Add support CDC devices
2026-04-23 Fixed GPIO pull-up mode
2026-04-23 Add status shows when WPS
2026-04-23 Add display info when WPS is enable
2026-04-24 Add configuration divider of ADC
2026-04-25 Add support CDC device for raspberry Pi
2026-04-28 Add SSD1306 Display
2026-04-29 Change default password
2026-04-29 Add how to create bin file
2026-04-29 Add binary for XIAO-ESP32S3
2026-04-29 Add mini display
2026-04-30 Fixed WiFi connection is slow with WPS enabled
2026-04-30 Fixed WPS connection is failed
2026-04-30 Fixed WPS connection
2026-05-01 Serial UART pins are pulled up
2026-05-09 Add HW schematic as KiCad
2026-05-11 Update ST7789V new 8pin foot print
2026-05-14 Fixed to reconnect WiFi AP when it is failed
2026-05-15 Fixed hangs when use WPS on TP-Link
2026-05-18 wifi: fix WPS credential capture when ap_cred_cnt > 0
    When WPS succeeds via the ap_cred_cnt > 0 path, esp_wifi_get_config()
    may not have the passphrase populated at the time the poll loop reads
    it, causing an empty password and a failed connection attempt.
    Fix by capturing SSID and passphrase directly from event_data->ap_cred[0]
    inside wps_event_handler (guarded by a null-check and ap_cred_cnt > 0).
    The credentials are stored in static buffers (WPS_SSID_BUF / WPS_PASS_BUF)
2026-06-11 mini_display: add overlay message API and reduce refresh interval to 250ms
    - Add MINI_MESSAGE static mutex for overlay (title, body) state
    - Add show_message() and clear_message() public functions
    - Render overlay when set; fall back to normal info display otherwise
    - Reduce sleep from 1s to 250ms for responsive overlay updates
2026-06-11 btn_ctrl: show factory reset countdown on mini display
    - Show overlay starting at 5s hold (1s earlier than serial display)
    - Update countdown every second until FACTORY_RESET_PRESS_MS
    - Clear overlay via mini_display::clear_message() on button release
    - Track mini_display_updated flag alongside existing display_updated
2026-06-11 wifi: use raw pointers for WPS static buffer access to avoid UB
    - Use copy_nonoverlapping instead of slice assignment in wps_event_handler
    - Copy WPS_SSID_BUF/WPS_PASS_BUF into local arrays before reading in
    wifi_connect_wps to eliminate shared references to mutable statics
2026-06-11 main: show WPS connection status on mini display
    - Call mini_display::show_message() before starting WPS PBC
    - Call mini_display::clear_message() after WPS succeeds or fails
    - Refactor wifi_connect_wps result into local variable to allow cleanup
2026-06-11 Cargo.lock: update for version bump to 0.1.1
2026-06-11 ssh_bridge: drain wolfSSH channel buffer in a loop to fix large-paste echo
    wolfSSH_ChannelIdRead() returns at most sizeof(buf)=512 bytes per call.
    When a user pastes a long string, the entire payload arrives in one
    wolfSSH_worker() → WS_CHAN_RXD cycle. The previous code read only the
    first 512 bytes and forwarded them to the serial device; the remainder
    stayed in wolfSSH's internal channel buffer. On the next loop
    iteration wolfSSH_worker() finds nothing new on the non-blocking socket
2026-06-11 fix: use stable toolchain for cargo installs in setup script
2026-06-11 docs: use board-specific cfg.toml copy instructions
2026-06-11 feat: add board-specific cfg templates
2026-06-12 Add build image script

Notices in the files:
hw/mini-ssh-serial-bridge/min-ssh-serial-bridge.kicad_sch:
Licensed under CC-BY-SA V4.0
(C) 2026 Hiroshi Nakajima
hw/ssh-bridge-for-raspberrypi.kicad_pcb:
(C) 2026 HNZ
